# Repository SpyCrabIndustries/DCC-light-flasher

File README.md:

# DCC-light-flasher
DCC light flasher PCB

this is a quick and dirty PCB for at attiny85 based DCC decoder for turning lights on on rolling stock ect. right now all the markdown and files are kinda a mess.
if aanyone wants to sort it and make a PR be my guest ;3 

currently the only thing up here was made to do this: https://www.youtube.com/watch?v=XgUUQQwzfhY 
gerber files are in the folder labeled gerber.
the schematic & BOM is in the folder labeled schematic !!!check the schematic befor fabbing this i have not tested it!!! 
the whole kicad folde is also up here so yall can mess with it if you'd like.

have fun! ill clean this up at some point (lol, famous last words)

oh, and if something needs to be changed let me know

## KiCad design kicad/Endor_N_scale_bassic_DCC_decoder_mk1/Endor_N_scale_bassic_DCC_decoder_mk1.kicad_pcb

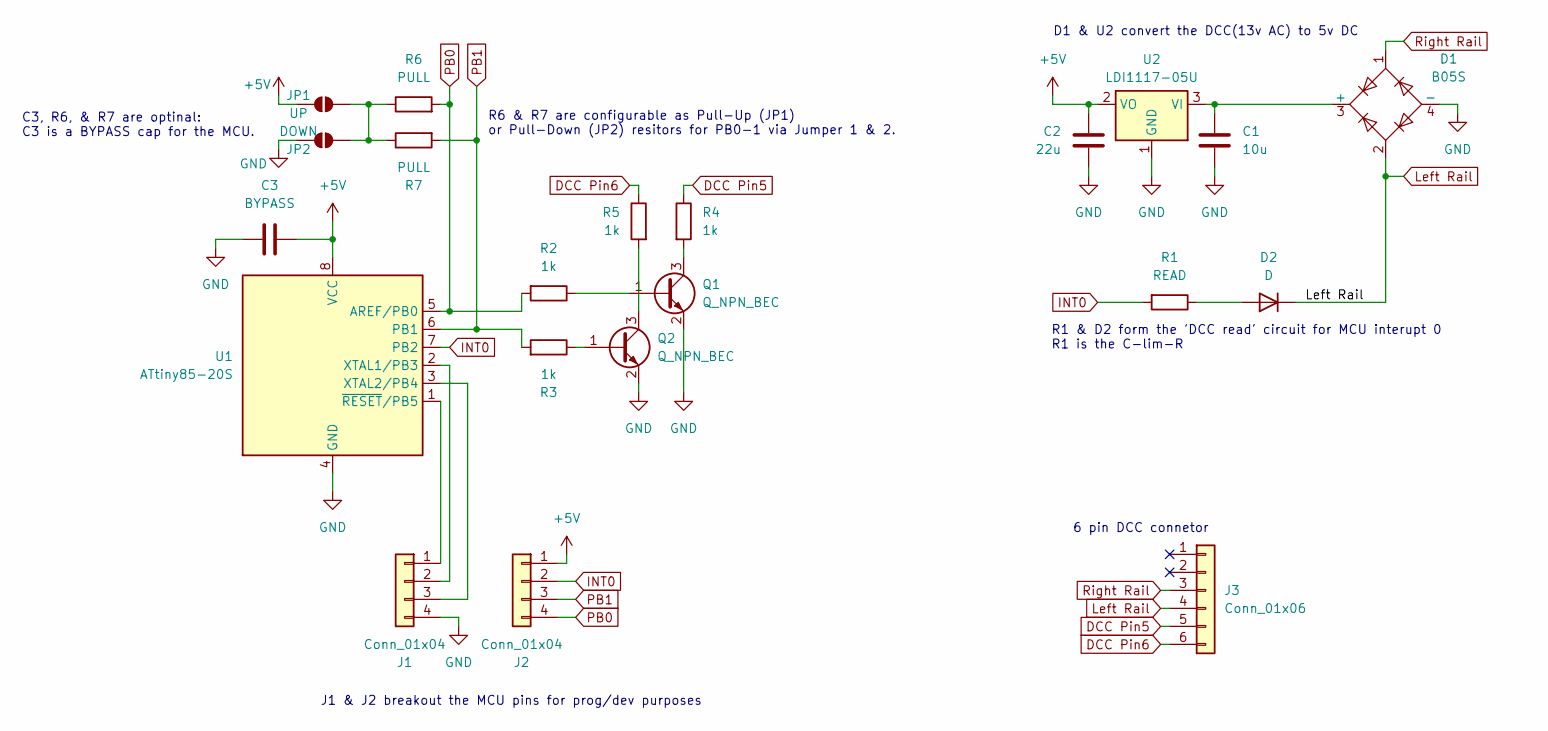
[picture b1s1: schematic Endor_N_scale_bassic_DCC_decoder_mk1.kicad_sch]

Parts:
C1: 10u; C_0805_2012Metric_Pad1.18x1.45mm_HandSolder
C2: 22u; C_0805_2012Metric_Pad1.18x1.45mm_HandSolder
C3: BYPASS; C_0805_2012Metric_Pad1.18x1.45mm_HandSolder
D1: B05S; TO-269AA
D2: D; D_SOD-123
J1, J2: Conn_01x04; PinHeader_1x04_P1.27mm_Vertical
J3: Conn_01x06; PinHeader_1x06_P1.27mm_Vertical
JP1: UP; SolderJumper-2_P1.3mm_Open_TrianglePad1.0x1.5mm
JP2: DOWN; SolderJumper-2_P1.3mm_Open_TrianglePad1.0x1.5mm
Q1, Q2: Q_NPN_BEC; SOT-23_Handsoldering
R1: READ; R_0805_2012Metric_Pad1.20x1.40mm_HandSolder
R2, R3, R4, R5: 1k; R_0805_2012Metric_Pad1.20x1.40mm_HandSolder
R6, R7: PULL; R_0805_2012Metric_Pad1.20x1.40mm_HandSolder
U1: ATtiny85-20S; SOIC-8_5.3x5.3mm_P1.27mm
U2: LDI1117-05U; SOT-89-3_Handsoldering

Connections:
+5V: C2.1, C3.2, J2.1, JP1.1 (A), U1.8 (VCC), U2.2 (VO); also elsewhere on the board
DCC Pin5: J3.5, R4.1
DCC Pin6: J3.6, R5.1
GND: C1.2, C2.2, C3.1, D1.4 (-), J1.4, JP2.1 (A), Q1.2 (E), Q2.2 (E), U1.4 (GND), U2.1 (GND); also elsewhere on the board
INT0: J2.2, R1.2, U1.7 (PB2)
Left Rail: D1.2, D2.1 (K), J3.4
unnamed: C1.1, D1.3 (+), U2.3 (VI)
unnamed: D2.2 (A), R1.1
unnamed: J1.1, U1.1 (~RESET/PB5)
unnamed: J1.2, U1.2 (XTAL1/PB3)
unnamed: J1.3, U1.3 (XTAL2/PB4)
unnamed 11: JP1.2 (B), JP2.2 (B), R6.1, R7.1; also elsewhere on the board
unnamed: Q1.1 (B), R2.1
unnamed: Q1.3 (C), R4.2
unnamed: Q2.1 (B), R3.1
unnamed: Q2.3 (C), R5.2
PB0: J2.4, R2.2, R6.2, U1.5 (AREF/PB0)
PB1: J2.3, R3.2, R7.2, U1.6 (PB1)
Right Rail: D1.1, J3.3

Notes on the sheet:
R6 & R7 are configurable as Pull-Up (JP1) or Pull-Down (JP2) resitors for PB0-1 via Jumper 1 & 2.
D1 & U2 convert the DCC(13v AC) to 5v DC
6 pin DCC connetor
R1 & D2 form the 'DCC read' circuit for MCU interupt 0 R1 is the C-lim-R
J1 & J2 breakout the MCU pins for prog/dev purposes
C3, R6, & R7 are optinal: C3 is a BYPASS cap for the MCU.

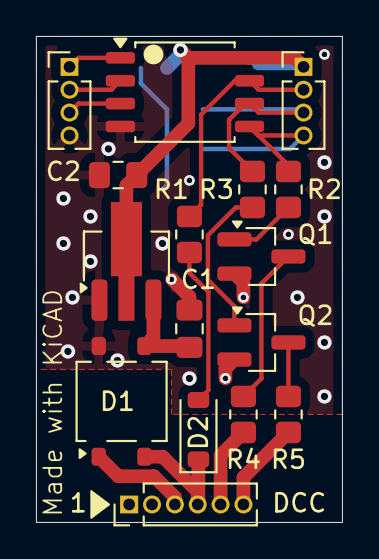
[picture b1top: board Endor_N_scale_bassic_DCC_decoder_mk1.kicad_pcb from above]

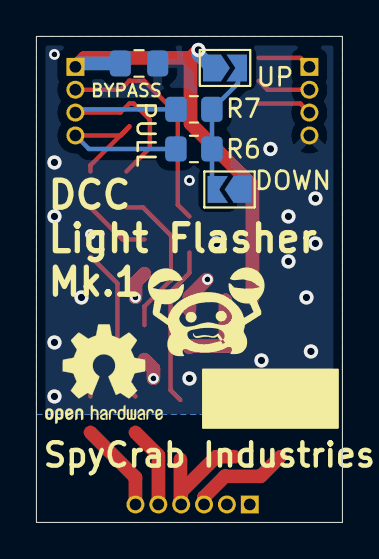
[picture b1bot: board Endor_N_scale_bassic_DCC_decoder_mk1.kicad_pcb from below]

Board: 2 copper layers, 17.0 x 27.0 mm, 21 parts (5 on the bottom side), 19 nets.

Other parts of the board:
DOWN: DOWN; SolderJumper-2_P1.3mm_Open_TrianglePad1.0x1.5mm
UP: UP; SolderJumper-2_P1.3mm_Open_TrianglePad1.0x1.5mm

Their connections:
+5V: UP.1 (A); also elsewhere on the board
GND: DOWN.1 (A); also elsewhere on the board
unnamed 11: DOWN.2 (B), UP.2 (B); also elsewhere on the board

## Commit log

2025-11-25 added everthing
2025-11-25 fixed image
2025-11-25 added kicad file, fixed image?
